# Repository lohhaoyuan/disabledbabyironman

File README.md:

# disabledbabyironman
Design files for 2026 CenTAD Project LM05

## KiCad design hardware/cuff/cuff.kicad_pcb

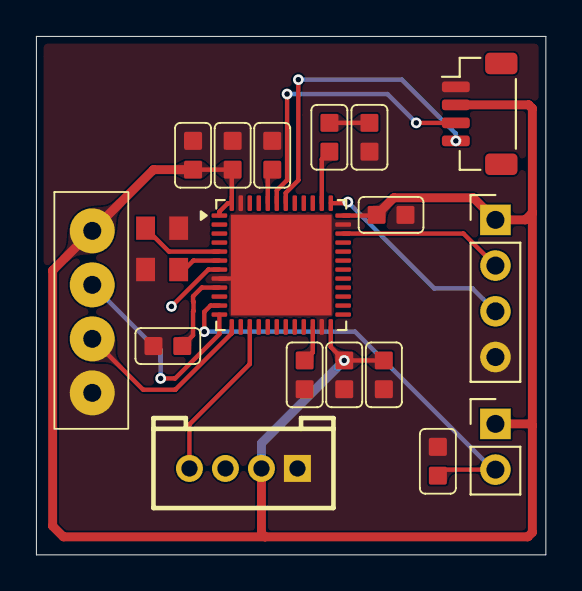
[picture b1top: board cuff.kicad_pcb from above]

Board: 2 copper layers, 28.3 x 28.8 mm, 18 parts (0 on the bottom side), 16 nets.

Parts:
C301: 2u2; cap0603
C302, C303, C304, C305, C306, C307: 0u1; cap0603
D301: RED; led0603
J1: FSR 1; PinHeader_1x02_P2.54mm_Vertical
J2: IMU SH; JST_SH_BM04B-SRSS-TB_1x04-1MP_P1.00mm_Vertical
J3: Conn_01x04; Untitled
J4: stupid grove connector; GROVE-HW4-2.0
J302: Conn_01x04; PinHeader_1x04_P2.54mm_Vertical
MAIN501: STM32F411CEUx; QFN-48-1EP_7x7mm_P0.5mm_EP5.6x5.6mm
R1: 10k; res0603
R301: 1K; res0603
R302: 10K; res0603
Y301: 16Mhz; CX3225SB16000D0FPLCC

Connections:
+3V3: C301.1, C302.1, C303.1, C304.1, C305.1, C306.1, J1.1, J2.2, J3.1, J4.2, J302.1, MAIN501.1 (VBAT), MAIN501.9 (VDDA), MAIN501.24 (VDD), MAIN501.36 (VDD), MAIN501.48 (VDD)
/BOOT0: MAIN501.44 (BOOT0), R302.2
/Box RX: J3.2, MAIN501.12 (PA2)
/Box TX: J3.3, MAIN501.13 (PA3)
/EMG SIG: J4.4, MAIN501.15 (PA5)
/FSR 1: J1.2, MAIN501.11 (PA1), R1.1
/IMU SCL: J2.4, MAIN501.42 (PB6)
/IMU SDA: J2.3, MAIN501.43 (PB7)
/LED: D301.2 (A), MAIN501.38 (PA15)
/OSC IN: MAIN501.5 (PH0), Y301.1
/OSC OUT: MAIN501.6 (PH1), Y301.3
/SWCLK: J302.3, MAIN501.37 (PA14)
/SWDIO: J302.2, MAIN501.34 (PA13)
GNDREF: C301.2, C302.2, C303.2, C304.2, C305.2, C306.2, C307.2, J2.1, J3.4, J4.1, J302.4, MAIN501.8 (VSSA), MAIN501.23 (VSS), MAIN501.35 (VSS), MAIN501.47 (VSS), MAIN501.49 (VSS), R1.2, R301.2, R302.1, Y301.2, Y301.4
unnamed: D301.1 (K), R301.1
unnamed: C307.1, MAIN501.22 (VCAP1)

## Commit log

2026-06-18 cuff
2026-06-18 software
2026-06-23 sean siew is a f4g
2026-06-23 remove teensy direct to pico
